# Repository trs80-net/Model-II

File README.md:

TRS80_M2_BlankBoards - KiCAD unpopulated MII boards WITH edge connectors.

TRS80_M2_CPU - KiCAD schematics of the CPU borad. WORK IN PROGRESS!  INCOMPLETE!

TRS80_M2_MB - KiCAD schematic and PCB of the MII mother board. COMPLETE

Z80_symbol.tar.gz - KiCAD Z-80 symbols needed for the above schematics.

ArfonSymbols.kicad_sym - KiCAD symbols that I created and used in these schematics.

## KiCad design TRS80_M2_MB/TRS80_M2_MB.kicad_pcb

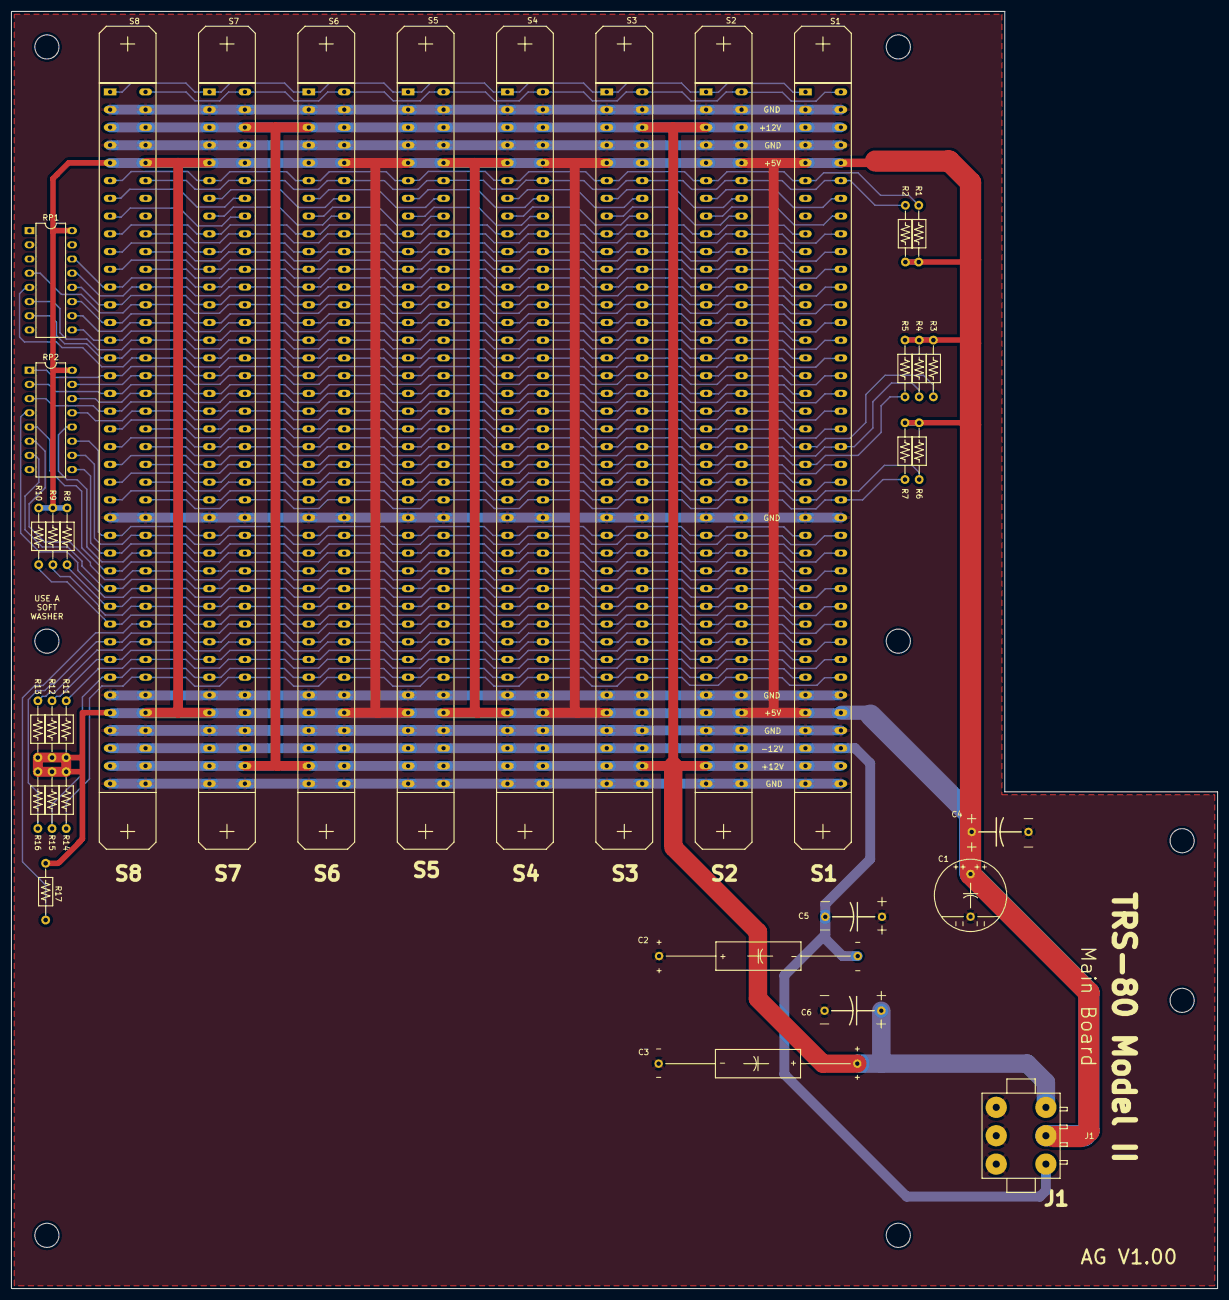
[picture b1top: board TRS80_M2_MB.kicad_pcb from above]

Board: 2 copper layers, 215.9 x 228.6 mm, 34 parts (0 on the bottom side), 72 nets.

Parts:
C1: 470uF 16V R; Capcitor Radial .300
C2: 470uf 16V A; Capcitor Axial 1.400
C3: 470uF 16V A; Capcitor Axial 1.400
C4, C5, C6: .1uf 50V; Capcitor .400
J1: TRS80M2-J1_power; TRS90-M2-J1power
R1, R2, R3, R4, R5, R6, R7, R8, R9, R10, R11, R12, R13, R14, R15, R16, R17: 2.2K .25W 5%; Resistor - horiz
RP1, RP2: Bourns 4116R-2-390; DIP-16pin-narrowpad
S1, S2, S3, S4, S5, S6, S7, S8: EDAC 346-080-521-804; EdgeConnector-125-80

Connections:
8MHz: S1.46, S2.46, S3.46, S4.46, S5.46, S6.46, S7.46, S8.46
+5V: C1.1, C4.1, J1.2 (+5V), R1.1, R2.1, R3.1, R4.1, R5.1, R6.1, R7.1, R8.1, R9.1, R10.1, R11.1, R12.1, R13.1, R14.1, R15.1, R16.1, R17.1, RP1.16, RP2.16, S1.9, S1.10, S1.71, S1.72, S2.9, S2.10, S2.71, S2.72, S3.9, S3.10, S3.71, S3.72, S4.9, S4.10, S4.71, S4.72, S5.9, S5.10, S5.71, S5.72, S6.9, S6.10, S6.71, S6.72, S7.9, S7.10, S7.71, S7.72, S8.9, S8.10, S8.71, S8.72
+12V: C3.1, C6.1, J1.1 (+12V), S1.5, S1.6, S1.77, S1.78, S2.5, S2.6, S2.77, S2.78, S3.5, S3.6, S3.77, S3.78, S4.5, S4.6, S4.77, S4.78, S5.5, S5.6, S5.77, S5.78, S6.5, S6.6, S6.77, S6.78, S7.5, S7.6, S7.77, S7.78, S8.5, S8.6, S8.77, S8.78
-12V: C2.2, C5.2, J1.3 (-12V), S1.75, S1.76, S2.75, S2.76, S3.75, S3.76, S4.75, S4.76, S5.75, S5.76, S6.75, S6.76, S7.75, S7.76, S8.75, S8.76
A00*: RP1.14, S1.23, S2.23, S3.23, S4.23, S5.23, S6.23, S7.23, S8.23
A01*: RP1.13, S1.24, S2.24, S3.24, S4.24, S5.24, S6.24, S7.24, S8.24
A02*: RP1.12, S1.25, S2.25, S3.25, S4.25, S5.25, S6.25, S7.25, S8.25
A03*: RP1.4, S1.26, S2.26, S3.26, S4.26, S5.26, S6.26, S7.26, S8.26
A04*: RP1.11, S1.27, S2.27, S3.27, S4.27, S5.27, S6.27, S7.27, S8.27
A05*: RP1.10, S1.28, S2.28, S3.28, S4.28, S5.28, S6.28, S7.28, S8.28
A06*: RP1.9, S1.29, S2.29, S3.29, S4.29, S5.29, S6.29, S7.29, S8.29
A07*: RP1.6, S1.30, S2.30, S3.30, S4.30, S5.30, S6.30, S7.30, S8.30
A08*: RP1.7, S1.31, S2.31, S3.31, S4.31, S5.31, S6.31, S7.31, S8.31
A09*: RP1.5, S1.32, S2.32, S3.32, S4.32, S5.32, S6.32, S7.32, S8.32
A10*: RP2.1, S1.33, S2.33, S3.33, S4.33, S5.33, S6.33, S7.33, S8.33
A11*: RP2.15, S1.34, S2.34, S3.34, S4.34, S5.34, S6.34, S7.34, S8.34
A12*: RP2.2, S1.35, S2.35, S3.35, S4.35, S5.35, S6.35, S7.35, S8.35
A13*: RP2.14, S1.36, S2.36, S3.36, S4.36, S5.36, S6.36, S7.36, S8.36
A14*: RP2.3, S1.37, S2.37, S3.37, S4.37, S5.37, S6.37, S7.37, S8.37
A15*: RP2.13, S1.38, S2.38, S3.38, S4.38, S5.38, S6.38, S7.38, S8.38
BUSRQ*: S1.17, S2.17, S3.17, S4.17, S5.17, S6.17, S7.17, S8.17
CLOCK: S1.44, S2.44, S3.44, S4.44, S5.44, S6.44, S7.44, S8.44
D0*: RP2.11, S1.51, S2.51, S3.51, S4.51, S5.51, S6.51, S7.51, S8.51
D1*: RP2.10, S1.52, S2.52, S3.52, S4.52, S5.52, S6.52, S7.52, S8.52
D2*: RP2.9, S1.53, S2.53, S3.53, S4.53, S5.53, S6.53, S7.53, S8.53
D3*: RP2.12, S1.54, S2.54, S3.54, S4.54, S5.54, S6.54, S7.54, S8.54
D4*: RP2.5, S1.55, S2.55, S3.55, S4.55, S5.55, S6.55, S7.55, S8.55
D5*: RP2.6, S1.56, S2.56, S3.56, S4.56, S5.56, S6.56, S7.56, S8.56
D6*: RP2.7, S1.57, S2.57, S3.57, S4.57, S5.57, S6.57, S7.57, S8.57
D7*: RP2.4, S1.58, S2.58, S3.58, S4.58, S5.58, S6.58, S7.58, S8.58
DISRO*: S1.40, S2.40, S3.40, S4.40, S5.40, S6.40, S7.40, S8.40
GND: C1.2, C2.1, C3.2, C4.2, C5.1, C6.2, J1.4 (GND), J1.5 (GND), J1.6 (GND), S1.3, S1.4, S1.7, S1.8, S1.49, S1.50, S1.69, S1.70, S1.73, S1.74, S1.79, S1.80, S2.3, S2.4, S2.7, S2.8, S2.49, S2.50, S2.69, S2.70, S2.73, S2.74, S2.79, S2.80, S3.3, S3.4, S3.7, S3.8, S3.49, S3.50, S3.69, S3.70, S3.73, S3.74, S3.79, S3.80, S4.3, S4.4, S4.7, S4.8, S4.49, S4.50, S4.69, S4.70, S4.73, S4.74, S4.79, S4.80, S5.3, S5.4, S5.7, S5.8, S5.49, S5.50, S5.69, S5.70, S5.73, S5.74, S5.79, S5.80, S6.3, S6.4, S6.7, S6.8, S6.49, S6.50, S6.69, S6.70, S6.73, S6.74, S6.79, S6.80, S7.3, S7.4, S7.7, S7.8, S7.49, S7.50, S7.69, S7.70, S7.73, S7.74, S7.79, S7.80, S8.3, S8.4, S8.7, S8.8, S8.49, S8.50, S8.69, S8.70, S8.73, S8.74, S8.79, S8.80
HALT*: R14.2, S1.68, S2.68, S3.68, S4.68, S5.68, S6.68, S7.68, S8.68
INTRQ*: R1.2, S1.11, S2.11, S3.11, S4.11, S5.11, S6.11, S7.11, S8.11
IOCYC*: S1.22, S2.22, S3.22, S4.22, S5.22, S6.22, S7.22, S8.22
KBIRQ*: R4.2, S1.42, S2.42, S3.42, S4.42, S5.42, S6.42, S7.42, S8.42
MEMCYC*: S1.21, S2.21, S3.21, S4.21, S5.21, S6.21, S7.21, S8.21
NMIRQ*: R2.2, S1.12, S2.12, S3.12, S4.12, S5.12, S6.12, S7.12, S8.12
unnamed: S1.14, S2.13
unnamed: S1.16, S2.15
unnamed: S2.14, S3.13
unnamed: S2.16, S3.15
unnamed: S3.14, S4.13
unnamed: S3.16, S4.15
unnamed: S4.14, S5.13
unnamed: S4.16, S5.15
unnamed: S5.14, S6.13
unnamed: S5.16, S6.15
unnamed: S6.14, S7.13
unnamed: S6.16, S7.15
unnamed: S7.14, S8.13
unnamed: S7.16, S8.15
RD*: S1.19, S2.19, S3.19, S4.19, S5.19, S6.19, S7.19, S8.19
REFRSH*: S1.45, S2.45, S3.45, S4.45, S5.45, S6.45, S7.45, S8.45
RES: S1.39, S2.39, S3.39, S4.39, S5.39, S6.39, S7.39, S8.39
RES1: R8.2, S1.59, S2.59, S3.59, S4.59, S5.59, S6.59, S7.59, S8.59
RES2: R9.2, S1.60, S2.60, S3.60, S4.60, S5.60, S6.60, S7.60, S8.60
RES3: R10.2, S1.61, S2.61, S3.61, S4.61, S5.61, S6.61, S7.61, S8.61
RES4: R17.2, S1.62, S2.62, S3.62, S4.62, S5.62, S6.62, S7.62, S8.62
RES5: R16.2, S1.63, S2.63, S3.63, S4.63, S5.63, S6.63, S7.63, S8.63
RES6: R13.2, S1.64, S2.64, S3.64, S4.64, S5.64, S6.64, S7.64, S8.64
RES7: R12.2, S1.65, S2.65, S3.65, S4.65, S5.65, S6.65, S7.65, S8.65
RES8: R11.2, S1.66, S2.66, S3.66, S4.66, S5.66, S6.66, S7.66, S8.66
RESET*: R15.2, S1.67, S2.67, S3.67, S4.67, S5.67, S6.67, S7.67, S8.67
RTC: R6.2, S1.47, S2.47, S3.47, S4.47, S5.47, S6.47, S7.47, S8.47
SELECT*: R5.2, S1.43, S2.43, S3.43, S4.43, S5.43, S6.43, S7.43, S8.43
SYNC*: S1.18, S2.18, S3.18, S4.18, S5.18, S6.18, S7.18, S8.18
USER0: S1.1, S2.1, S3.1, S4.1, S5.1, S6.1, S7.1, S8.1
USER1: S1.2, S2.2, S3.2, S4.2, S5.2, S6.2, S7.2, S8.2
WAIT*: R7.2, S1.48, S2.48, S3.48, S4.48, S5.48, S6.48, S7.48, S8.48
WR*: S1.20, S2.20, S3.20, S4.20, S5.20, S6.20, S7.20, S8.20
XFERRQ: R3.2, S1.41, S2.41, S3.41, S4.41, S5.41, S6.41, S7.41, S8.41

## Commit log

2024-08-03 Create test
